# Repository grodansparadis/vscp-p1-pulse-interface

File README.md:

# vscp-p1-HAN-interface 

HAN P1 interface for smart meters to serial TTL. Should work with

| Meters |
| ------  |
| Sagemcom T211 / Ellevio & Skånska Energi |
| Landis+Gyr E360 |
| Itron A300 / Borås Elnät |
| S34U18 (Sanxing SX631) / Vattenfall |
| KAIFA MA304H4**E** / Nacka Energi (Not **D** version which is modbus) |
| KAIFA CL109 / Öresundskraft |
| Kamstrup w/ HAN module / Trollhättan Energi |
| and more. |

There is a description [here](https://grodansparadis.com/wordpress/?p=5039) about my setup. 

The PCB, [assembled](https://frogshop.se/product/kort-for-han-p1-ttl-serieinterface-monterat/?v=f003c44deab6) or [bare](https://frogshop.se/product/kort-for-han-p1-ttl-serieinterface-omonterat/?v=f003c44deab6), can be bought from https://frogshop.se/  

Bare PCB or mounted PCB is available from THE VSCP shop.

Interface card for P1 based smartmeter to TTL serial interface.  

## BOM

| Component | Description |
| --------- | ----------- |
| R1 | Resistor 4.7K 0805 |
| R2 | Resistor 10K 0805 |
| T1 | NPM Transistor BC847 |
| J1 | RJ11 Modular connector (Amphenol 54601 or similar) |
| J2 | 6-pin pinheader 2.54 pitch |
| J3 | 2-pin pinheader 2.54 pitch |

## J3 

Strap pins t use if the HAN interface does not provide power by itself.

## J2 Connections

| Pin | Description |
| --- | ----------- |
| 1 | +5V |
| 2 | +3.3V or 5V * |
| 3 | +3.3V or 5V * |
| 4 | Not Connected |
| 5 | RX (Received data TTL level) |
| 6 | GND |

* Use same power on 2/3 as the serial interface the unit is connected to.

## Connecting 

To connect the interface to a HAN P1 port a serial TTL interface is needed. We describe using an [USB to serial adapter](https://frogshop.se/product/usb-ttl-serial-adapter/?v=f003c44deab6) here but an Arduino or ESP8266/32 or similar can also be used.

First connect the interface to the serial adapter

| Interface | TTL adapter |
| --------- | ----------- |
| 1 | +5V |
| 2 | 3.3V |
| 3 | Not connected or 3.3V |
| 4 | Mot connected |
| 5 | RX |
| 6 | GND |

The following two pictures mau be clearer

Now draw a standard six leads RJ12 cable from the HAN port of the meter and connect it to the interface. 

The cable should have the same colors on both connectors (straight cable). Like this

It is OK to use a cable of a few meters. At least if you are in an environment without to much electric disturbance.

Now connect the TTL USB adapter to the serial port. The blue LED should light up on the USB TTL serial adapter. 

If everything is correct the red RX LED will light up every ten seconds to show that data is received.

Now you are ready to go. More info is [here](https://grodansparadis.com/wordpress/?p=5039) on how to proceed.

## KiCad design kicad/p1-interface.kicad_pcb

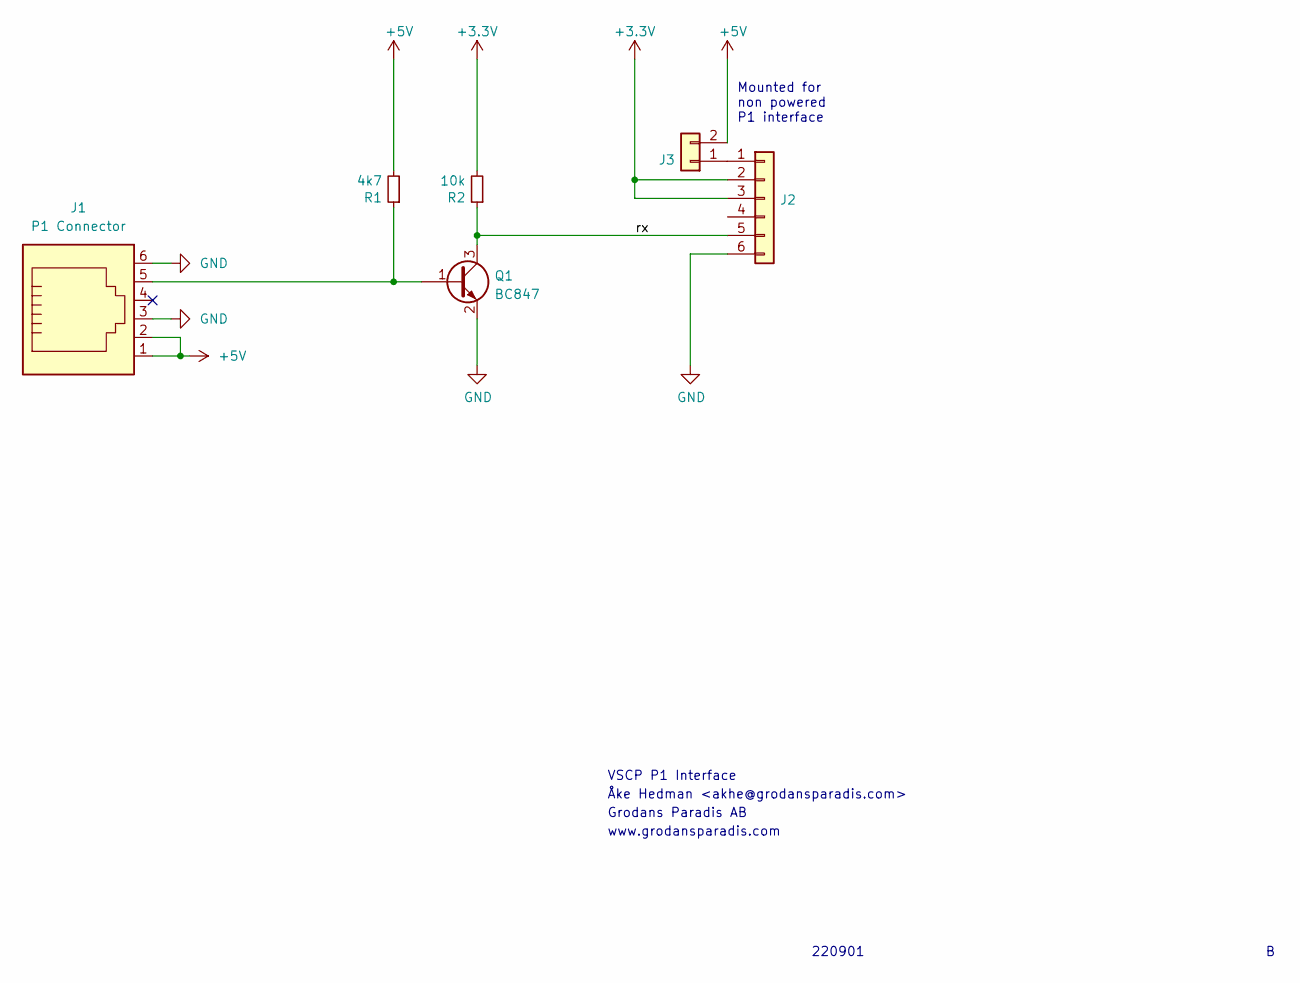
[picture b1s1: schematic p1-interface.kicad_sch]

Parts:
J1: P1 Connector; RJ12_Amphenol_54601
J2: Conn_01x06; PinHeader_1x06_P2.54mm_Vertical
J3: Conn_01x02; PinHeader_1x02_P2.54mm_Vertical
Q1: BC847; SOT-23
R1: 4k7; R_0805_2012Metric_Pad1.20x1.40mm_HandSolder
R2: 10k; R_0805_2012Metric_Pad1.20x1.40mm_HandSolder

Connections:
+3V3: J2.2, J2.3, R2.2
+5V: J1.1, J1.2, J3.2, R1.2
/rx: J2.5, Q1.3 (C), R2.1
GND: J1.3, J1.6, J2.6, Q1.2 (E)
unnamed: J1.5, Q1.1 (B), R1.1
unnamed: J2.1, J3.1

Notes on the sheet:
Mounted for non powered P1 interface
VSCP P1 Interface
Åke Hedman <akhe@grodansparadis.com>
www.grodansparadis.com
Grodans Paradis AB
220901

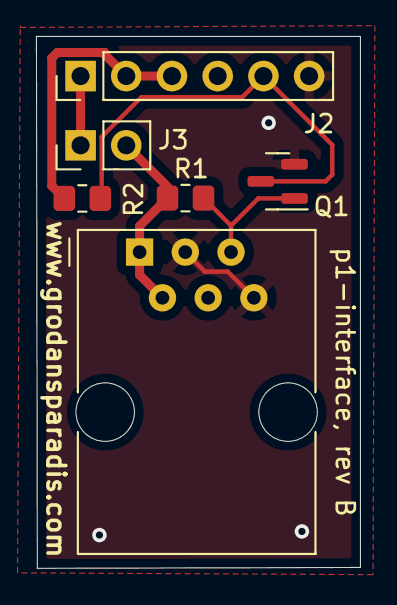
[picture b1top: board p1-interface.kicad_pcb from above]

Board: 2 copper layers, 18.0 x 29.5 mm, 6 parts (0 on the bottom side), 6 nets.

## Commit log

2022-09-02 Initial checkin
2022-09-02 Added image of card
2022-09-02 Added link to Grodan
2022-09-02 Changed faulty link
2022-09-15 Added picture of schema
2022-09-15 Fixed typo in readm
2022-09-15 Updated link to store
2022-09-19 Updated images and readme for rev B
2022-09-20 Added link to setup description
2022-10-20 Added setup instructions
2022-10-20 Added not about bug in Landis Gyr
2023-01-09 Updated copyright year
